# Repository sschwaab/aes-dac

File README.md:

# aes-dac
If you've ever found yourself running out of analog outputs on your digital mixer, you know the frustration. Maybe you have an extra stereo AES output—like we do—but no compatible gear to take it as an input.

That’s where this little device comes in. It takes the AES output of your console and converts it into a clean, balanced, line-level XLR signal (+4 dBu).

Sure, there are commercial solutions out there. But they often target high-end studio applications, making them unnecessarily expensive—sometimes costing as much as your entire mixer! We believe that great sound shouldn't come with an outrageous price tag.

Powered by a standard 9V power supply—just like your favorite guitar effects pedals—this device is easy to integrate into your setup. No frills, no overkill—just a simple and affordable solution that gets the job done.

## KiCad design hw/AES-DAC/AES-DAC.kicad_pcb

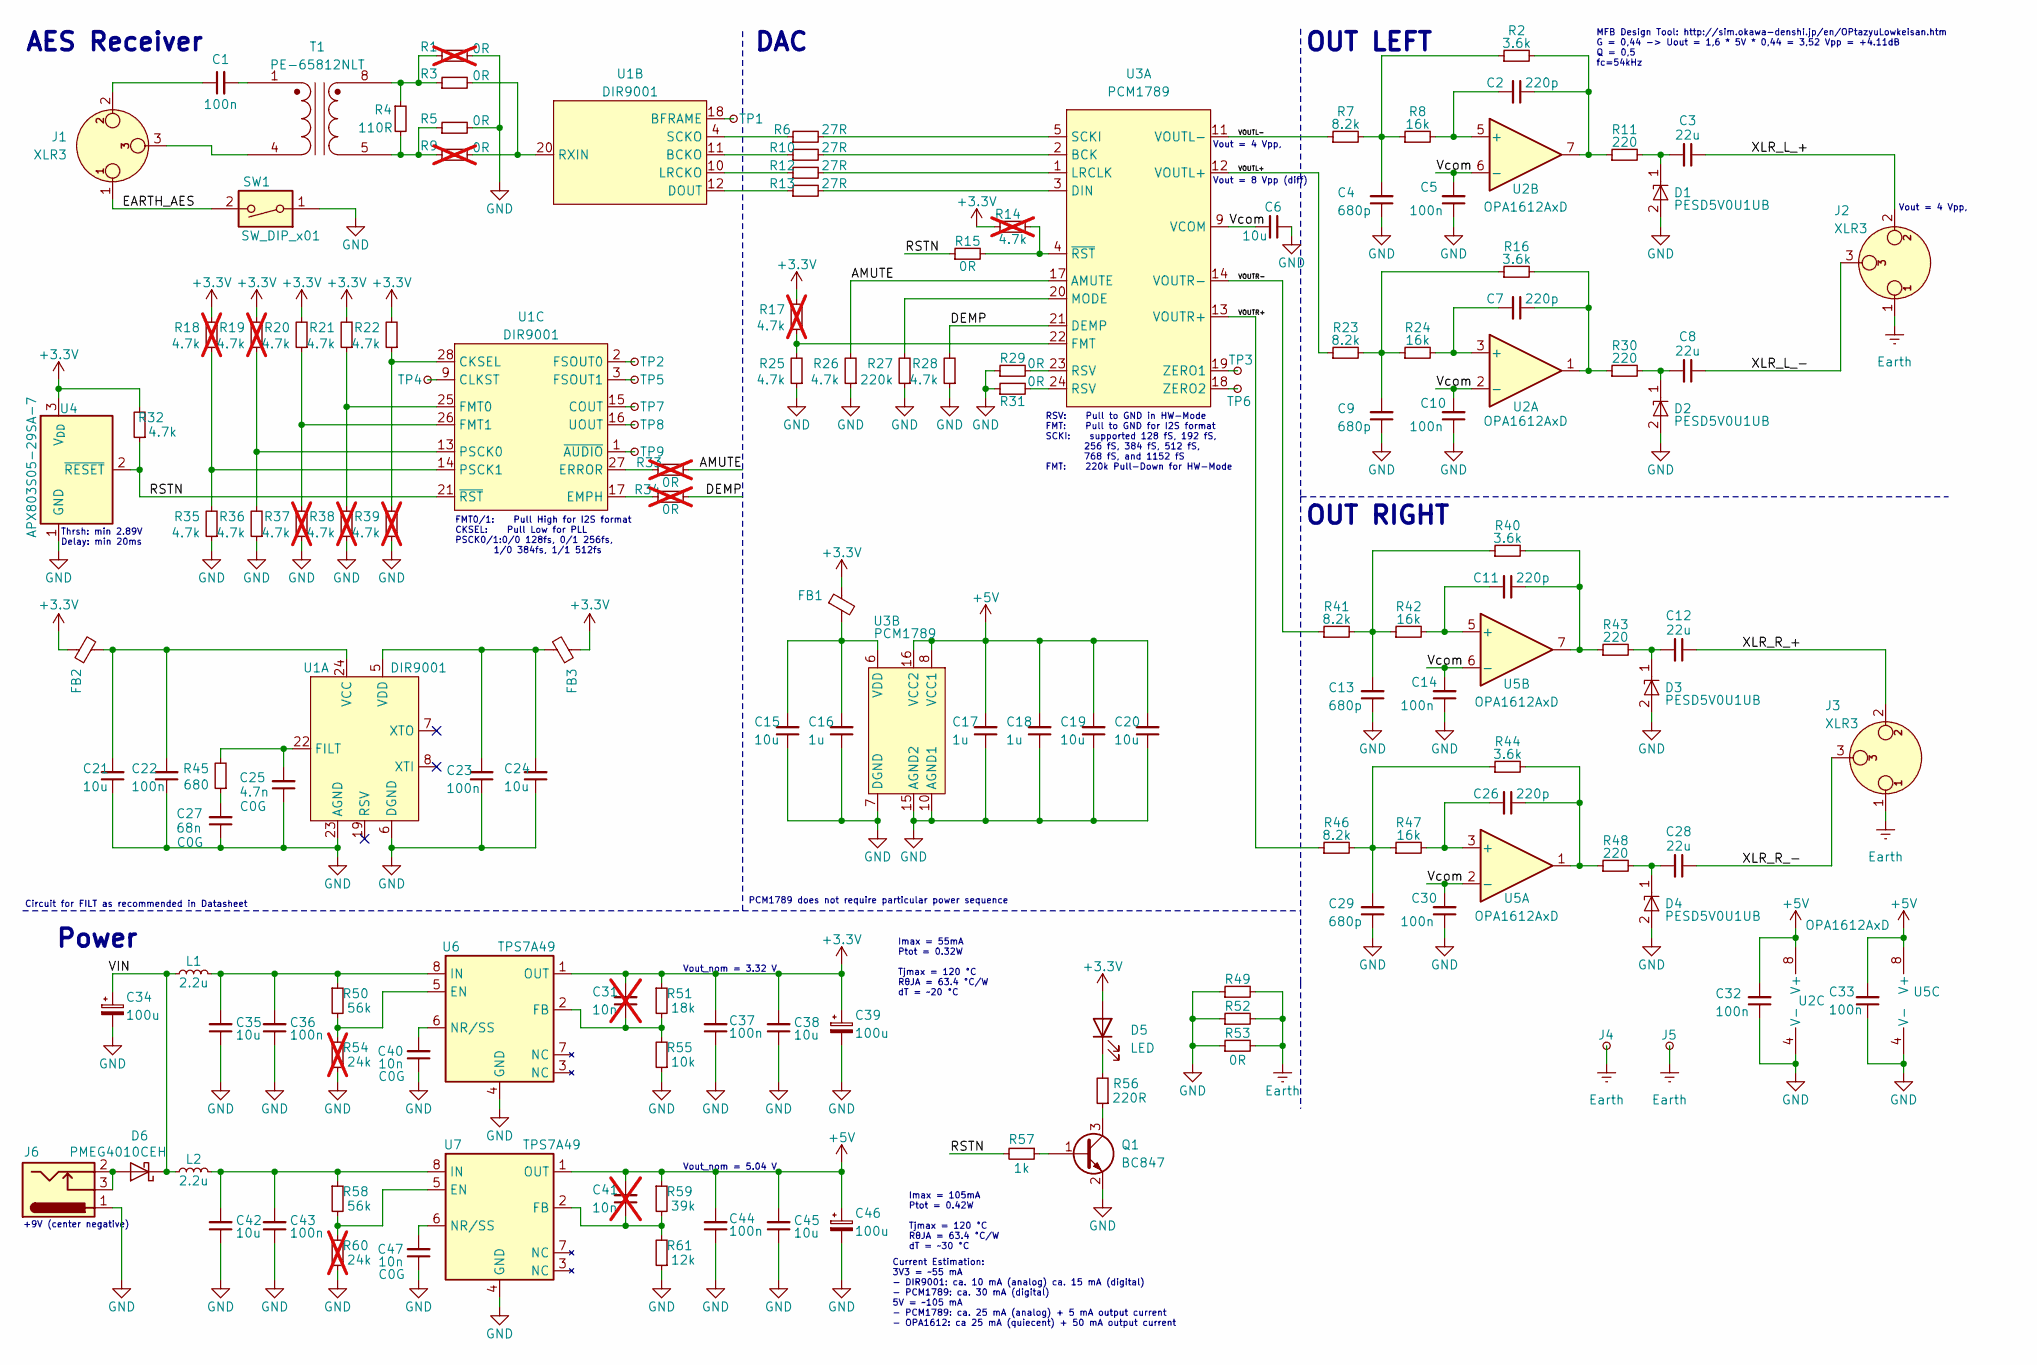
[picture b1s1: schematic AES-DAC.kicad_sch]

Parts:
C1, C5, C10, C14, C22, C23, C30, C32, C33, C36, C37, C43, C44: 100n; C_0805_2012Metric_Pad1.18x1.45mm_HandSolder
C2, C7, C11, C26: 220p; C_Rect_L7.2mm_W4.5mm_P5.00mm_FKS2_FKP2_MKS2_MKP2
C3, C8, C12, C28: 22u; C_Radial_D10.0mm_H12.5mm_P5.00mm
C4, C9, C13, C29: 680p; C_Rect_L7.2mm_W4.5mm_P5.00mm_FKS2_FKP2_MKS2_MKP2
C6, C15, C19, C20, C21, C24, C35, C38, C42, C45: 10u; C_0805_2012Metric_Pad1.18x1.45mm_HandSolder
C16, C17, C18: 1u; C_0805_2012Metric_Pad1.18x1.45mm_HandSolder
C25: 4.7n; C_0805_2012Metric_Pad1.18x1.45mm_HandSolder; LCSC Part C77063
C27: 68n; C_0805_2012Metric_Pad1.18x1.45mm_HandSolder; LCSC Part C77084
C31, C41: 10n; C_0805_2012Metric_Pad1.18x1.45mm_HandSolder; LCSC Part C97905; not fitted
C34, C39, C46: 100u; CP_Elec_6.3x7.7; LCSC Part C134220
C40, C47: 10n; C_0805_2012Metric_Pad1.18x1.45mm_HandSolder; LCSC Part C97905
D1, D2, D3, D4: PESD5V0U1UB; D_SOD-523; LCSC Part C2830317, C139613
D5: LED; LED_D3.0mm_Horizontal_O3.81mm_Z6.0mm
D6: PMEG4010CEH; D_SOD-123F
FB1: R_0805_2012Metric_Pad1.20x1.40mm_HandSolder
FB2, FB3: FerriteBead_Small; R_0805_2012Metric_Pad1.20x1.40mm_HandSolder
J1: XLR3; Jack_XLR_Neutrik_NC3FAH1-0_Horizontal
J2, J3: XLR3; Jack_XLR_Neutrik_NC3MAH-0_Horizontal
J4, J5: TestPoint_Small; TestPoint_THTPad_D2.0mm_Drill1.0mm
J6: DCJ200-10-A-K1-K; BarrelJack_GCT_DCJ200-10-A_Horizontal
L1, L2: 2.2u; L_1206_3216Metric
Q1: BC847; SOT-23
R1, R9, R33, R34: 0R; R_0603_1608Metric_Pad0.98x0.95mm_HandSolder; not fitted
R2, R16, R40, R44: 3.6k; R_0805_2012Metric_Pad1.20x1.40mm_HandSolder
R3, R5, R15, R29, R31: 0R; R_0603_1608Metric_Pad0.98x0.95mm_HandSolder
R4: 110R; C_0805_2012Metric_Pad1.18x1.45mm_HandSolder
R6, R10, R12, R13: 27R; R_0603_1608Metric_Pad0.98x0.95mm_HandSolder
R7, R23, R41, R46: 8.2k; R_0805_2012Metric_Pad1.20x1.40mm_HandSolder
R8, R24, R42, R47: 16k; R_0805_2012Metric_Pad1.20x1.40mm_HandSolder
R11, R30, R43, R48: 220; R_0805_2012Metric_Pad1.20x1.40mm_HandSolder
R14, R17, R18, R19, R37, R38, R39: 4.7k; R_0603_1608Metric_Pad0.98x0.95mm_HandSolder; not fitted
R20, R21, R22, R25, R26, R28, R32, R35, R36: 4.7k; R_0603_1608Metric_Pad0.98x0.95mm_HandSolder
R27: 220k; R_0603_1608Metric_Pad0.98x0.95mm_HandSolder
R45: 680; R_0805_2012Metric_Pad1.20x1.40mm_HandSolder
R49, R52, R53: 0R; R_0805_2012Metric_Pad1.20x1.40mm_HandSolder
R50, R58: 56k; R_0805_2012Metric_Pad1.20x1.40mm_HandSolder
R51: 18k; R_0805_2012Metric_Pad1.20x1.40mm_HandSolder
R54, R60: 24k; R_0805_2012Metric_Pad1.20x1.40mm_HandSolder; not fitted
R55: 10k; R_0805_2012Metric_Pad1.20x1.40mm_HandSolder
R56: 220R; R_0805_2012Metric_Pad1.20x1.40mm_HandSolder
R57: 1k; R_0603_1608Metric_Pad0.98x0.95mm_HandSolder
R59: 39k; R_0805_2012Metric_Pad1.20x1.40mm_HandSolder
R61: 12k; R_0805_2012Metric_Pad1.20x1.40mm_HandSolder
SW1: SW_DIP_x01; SW_DIP_SPSTx01_Slide_6.7x4.1mm_W6.73mm_P2.54mm_LowProfile_J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; LCSC Part C19272173
T1: PE-65812NLT
TP1, TP2, TP3, TP4, TP5, TP6, TP7, TP8, TP9: TestPoint_Small; TestPoint_Pad_D1.0mm
U1: DIR9001; TSSOP-28_4.4x9.7mm_P0.65mm
U2, U5: OPA1612AxD; SOIC-8_3.9x4.9mm_P1.27mm; LCSC Part C94590
U3: PCM1789; TSSOP-24_4.4x7.8mm_P0.65mm
U4: APX803S05-29SA-7; SOT-23; LCSC Part C2067629
U6, U7: TPS7A49; HVSSOP-8-1EP_3x3mm_P0.65mm_EP1.57x1.89mm_ThermalVias; LCSC Part C16430

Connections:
+3.3V: C31.2, C37.2, C38.2, C39.1, D5.2 (A), FB1.1, FB2.1, FB3.1, R14.1, R17.2, R18.2, R19.2, R20.2, R21.2, R22.2, R32.2, R51.1, U4.3 (V_{DD}), U6.1 (OUT)
+5V: C17.2, C18.2, C19.2, C20.2, C32.2, C33.2, C41.2, C44.2, C45.2, C46.1, R59.1, U2.8 (V+), U3.8 (VCC1), U3.16 (VCC2), U5.8 (V+), U7.1 (OUT)
/AMUTE: R26.2, R33.2, U3.17 (AMUTE)
/DEMP: R28.2, R34.2, U3.21 (DEMP)
/EARTH_AES: J1.1, SW1.2
/RSTN: R15.1, R32.1, R57.2, U1.21 (~RST), U4.2 (~RESET)
/VIN: C34.1, D6.1 (K), L1.1, L2.1
/VOUTL+: R23.1, U3.12 (VOUTL+)
/VOUTL-: R7.1, U3.11 (VOUTL-)
/VOUTR+: R46.1, U3.13 (VOUTR+)
/VOUTR-: R41.1, U3.14 (VOUTR-)
/Vcom: C5.2, C6.2, C10.2, C14.2, C30.2, U2.2 (-), U2.6 (-), U3.9 (VCOM), U5.2 (-), U5.6 (-)
/XLR_L_+: C3.1, J2.2
/XLR_L_-: C8.1, J2.3
/XLR_R_+: C12.1, J3.2
/XLR_R_-: C28.1, J3.3
Earth: J2.1, J3.1, J4.1, J5.1, R49.2, R52.2, R53.2
GND: C4.1, C5.1, C6.1, C9.1, C10.1, C13.1, C14.1, C15.1, C16.1, C17.1, C18.1, C19.1, C20.1, C21.1, C22.1, C23.1, C24.1, C25.1, C27.1, C29.1, C30.1, C32.1, C33.1, C34.2, C35.1, C36.1, C37.1, C38.1, C39.2, C40.1, C42.1, C43.1, C44.1, C45.1, C46.2, C47.1, D1.2, D2.2, D3.2, D4.2, J6.1, Q1.2 (E), R1.2, R5.2, R25.1, R26.1, R27.1, R28.1, R29.1, R31.1, R35.1, R36.1, R37.1, R38.1, R39.1, R49.1, R52.1, R53.1, R54.2, R55.1, R60.2, R61.1, SW1.1, U1.6 (DGND), U1.23 (AGND), U2.4 (V-), U3.7 (DGND), U3.10 (AGND1), U3.15 (AGND2), U4.1 (GND), U5.4 (V-), U6.4 (GND), U6.9 (GND), U7.4 (GND), U7.9 (GND)
unnamed: C1.1, J1.2
unnamed: C1.2, T1.1
unnamed: C2.1, R2.2, R11.1, U2.7
unnamed: C3.2, D1.1, R11.2
unnamed: C4.2, R2.1, R7.2, R8.1
unnamed: C7.1, R16.2, R30.1, U2.1
unnamed: C8.2, D2.1, R30.2
unnamed: C9.2, R16.1, R23.2, R24.1
unnamed: C11.1, R40.2, R43.1, U5.7
unnamed: C12.2, D3.1, R43.2
unnamed: C13.2, R40.1, R41.2, R42.1
unnamed: C26.1, R44.2, R48.1, U5.1
unnamed: C27.2, R45.1
unnamed: C28.2, D4.1, R48.2
unnamed: C29.2, R44.1, R46.2, R47.1
unnamed: D5.1 (K), R56.2
unnamed: D6.2 (A), J6.2, J6.3
unnamed: J1.3, T1.4
unnamed: Q1.1 (B), R57.1
unnamed: Q1.3 (C), R56.1
unnamed: R1.1, R3.1, R4.1, T1.8
unnamed: R4.2, R5.1, R9.1, T1.5
unnamed: R29.2, U3.23 (RSV)
unnamed: R31.2, U3.24 (RSV)
unnamed: C25.2, R45.2, U1.22 (FILT)
unnamed: C21.2, C22.2, FB2.2, U1.24 (VCC)
unnamed: C23.2, C24.2, FB3.2, U1.5 (VDD)
unnamed: R10.1, U1.11 (BCKO)
unnamed: TP1.1, U1.18 (BFRAME)
unnamed: R13.1, U1.12 (DOUT)
unnamed: R12.1, U1.10 (LRCKO)
unnamed: R3.2, R9.2, U1.20 (RXIN)
unnamed: R6.1, U1.4 (SCKO)
unnamed: R22.1, R39.2, U1.28 (CKSEL)
unnamed: TP4.1, U1.9 (CLKST)
unnamed: TP7.1, U1.15 (COUT)
unnamed: R34.1, U1.17 (EMPH)
unnamed: R33.1, U1.27 (ERROR)
unnamed: R21.1, R38.2, U1.25 (FMT0)
unnamed: R20.1, R37.2, U1.26 (FMT1)
unnamed: TP2.1, U1.2 (FSOUT0)
unnamed: TP5.1, U1.3 (FSOUT1)
unnamed: R19.1, R36.2, U1.13 (PSCK0)
unnamed: R18.1, R35.2, U1.14 (PSCK1)
unnamed: TP8.1, U1.16 (UOUT)
unnamed: TP9.1, U1.1 (~AUDIO)
unnamed: C7.2, R24.2, U2.3 (+)
unnamed: C2.2, R8.2, U2.5 (+)
unnamed: R10.2, U3.2 (BCK)
unnamed: R13.2, U3.3 (DIN)
unnamed: R17.1, R25.2, U3.22 (FMT)
unnamed: R12.2, U3.1 (LRCLK)
unnamed: R27.2, U3.20 (MODE)
unnamed: R6.2, U3.5 (SCKI)
unnamed: TP3.1, U3.19 (ZERO1)
unnamed: TP6.1, U3.18 (ZERO2)
unnamed: R14.2, R15.2, U3.4 (~RST)
unnamed: C15.2, C16.2, FB1.2, U3.6 (VDD)
unnamed: C26.2, R47.2, U5.3 (+)
unnamed: C11.2, R42.2, U5.5 (+)
unnamed: R50.2, R54.1, U6.5 (EN)
unnamed: C31.1, R51.2, R55.2, U6.2 (FB)
unnamed: C35.2, C36.2, L1.2, R50.1, U6.8 (IN)
unnamed: C40.2, U6.6 (NR/SS)
unnamed: R58.2, R60.1, U7.5 (EN)
unnamed: C41.1, R59.2, R61.2, U7.2 (FB)
unnamed: C42.2, C43.2, L2.2, R58.1, U7.8 (IN)
unnamed: C47.2, U7.6 (NR/SS)

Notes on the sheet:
Current Estimation: 3V3 = ~55 mA - DIR9001: ca. 10 mA (analog) ca. 15 mA (digital) - PCM1789: ca. 30 mA (digital) 5V = ~105 mA - PCM1789: ca. 25 mA (analog) + 5 mA output current - OPA1612: ca 25 mA (quiecent) + 50 mA output current
PCM1789 does not require particular power sequence
DAC
Power
OUT LEFT
Imax = 105mA Ptot = 0.42W Tjmax = 120 °C RθJA = 63.4 °C/W dT = ~30 °C
+9V (center negative)
Vout_nom = 3.32 V
Vout = 4 Vpp,
Vout = 8 Vpp (diff)
Thrsh: min 2.89V Delay: min 20ms
OUT RIGHT
RSV: Pull to GND in HW-Mode FMT: Pull to GND for I2S format SCKI: supported 128 fS, 192 fS, 256 fS, 384 fS, 512 fS, 768 fS, and 1152 fS FMT: 220k Pull-Down for HW-Mode
AES Receiver
MFB Design Tool: http://sim.okawa-denshi.jp/en/OPtazyuLowkeisan.htm G = 0,44 -> Uout = 1,6 * 5V * 0,44 = 3,52 Vpp = +4.11dB Q = 0,5 fc=54kHz
Circuit for FILT as recommended in Datasheet
Imax = 55mA Ptot = 0.32W Tjmax = 120 °C RθJA = 63.4 °C/W dT = ~20 °C
Vout_nom = 5.04 V
FMT0/1: Pull High for I2S format CKSEL: Pull Low for PLL PSCK0/1:0/0 128fs, 0/1 256fs, 1/0 384fs, 1/1 512fs

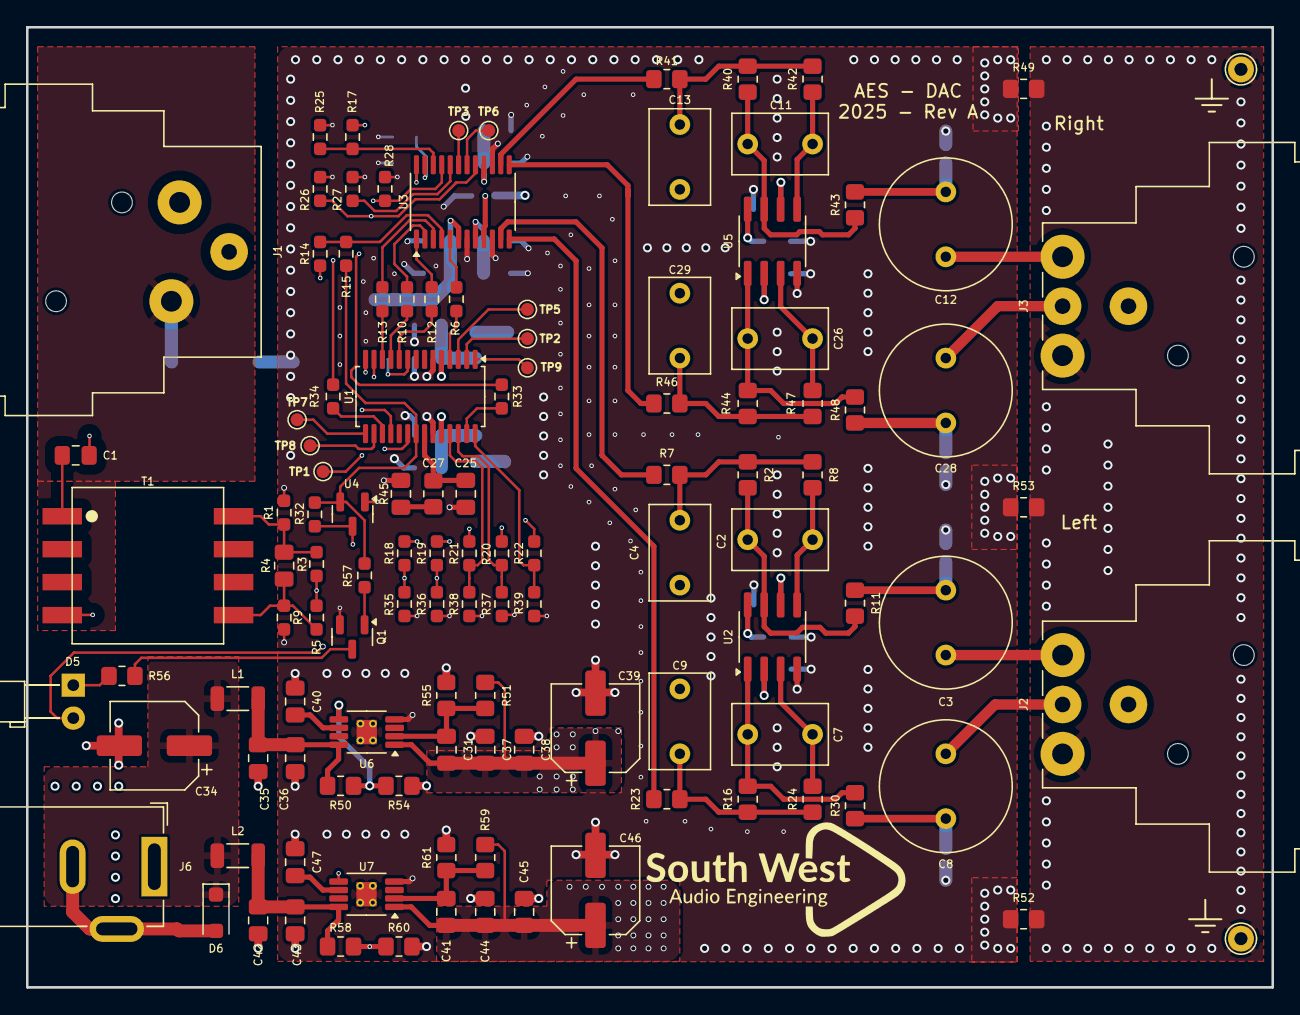
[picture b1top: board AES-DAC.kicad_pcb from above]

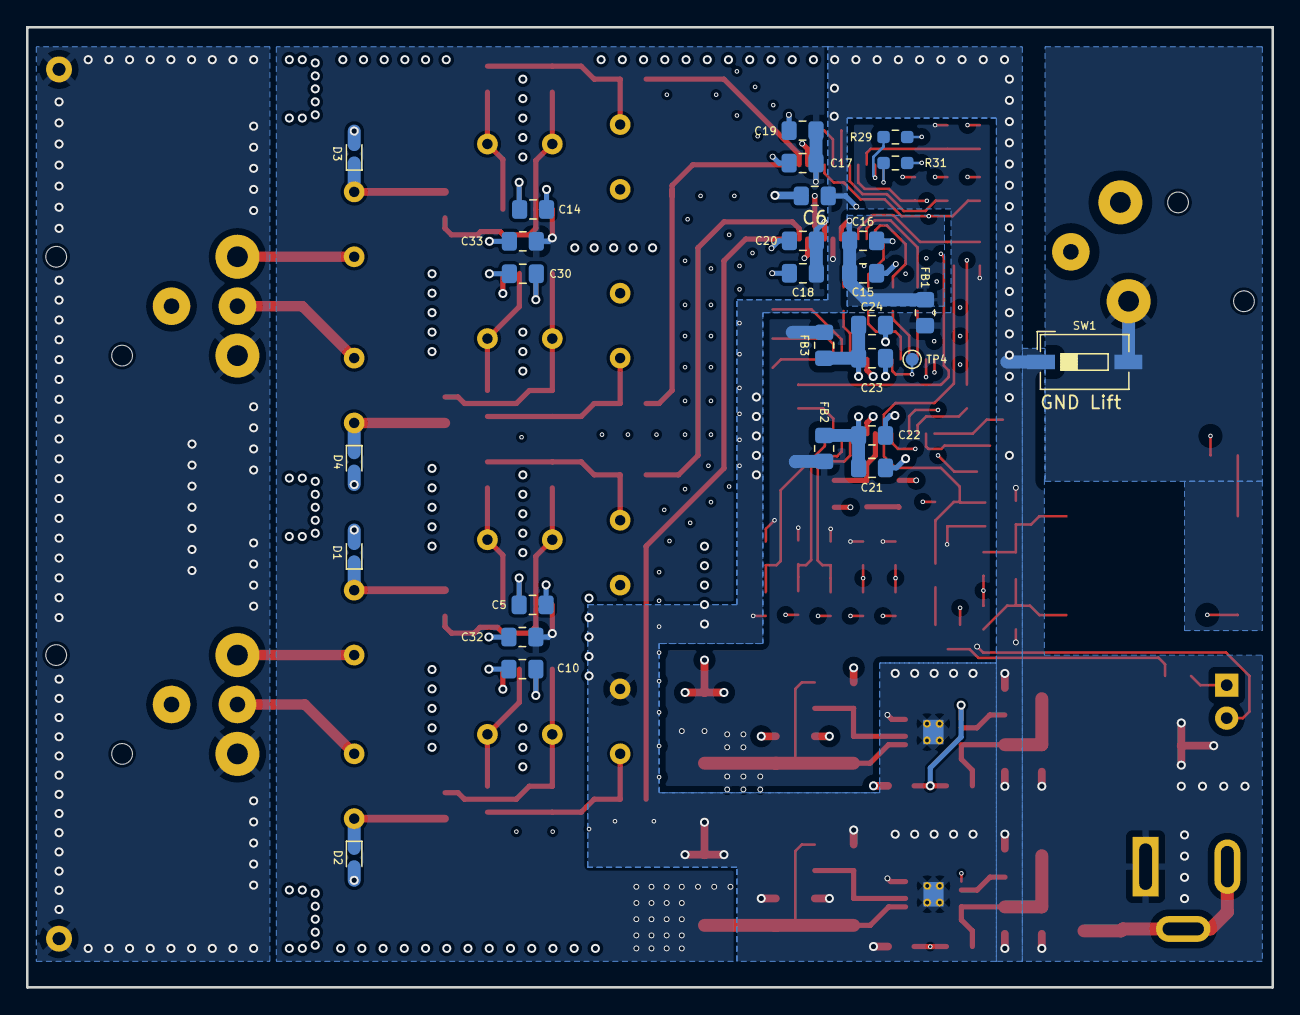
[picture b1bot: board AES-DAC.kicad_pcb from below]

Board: 4 copper layers, 96.0 x 74.0 mm, 144 parts (28 on the bottom side), 86 nets.

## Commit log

2025-02-15 First commit. Schematic first version done.
2025-02-16 minor corrections in schematic
2025-02-16 wrong orientation of schematic
2025-02-16 Annotated schematic
2025-02-23 Added: Simulation for Jitter analysis PCB File Updated: Schematic
2025-03-07 layout update
2025-04-13 Added Gerbers and did some improvements
